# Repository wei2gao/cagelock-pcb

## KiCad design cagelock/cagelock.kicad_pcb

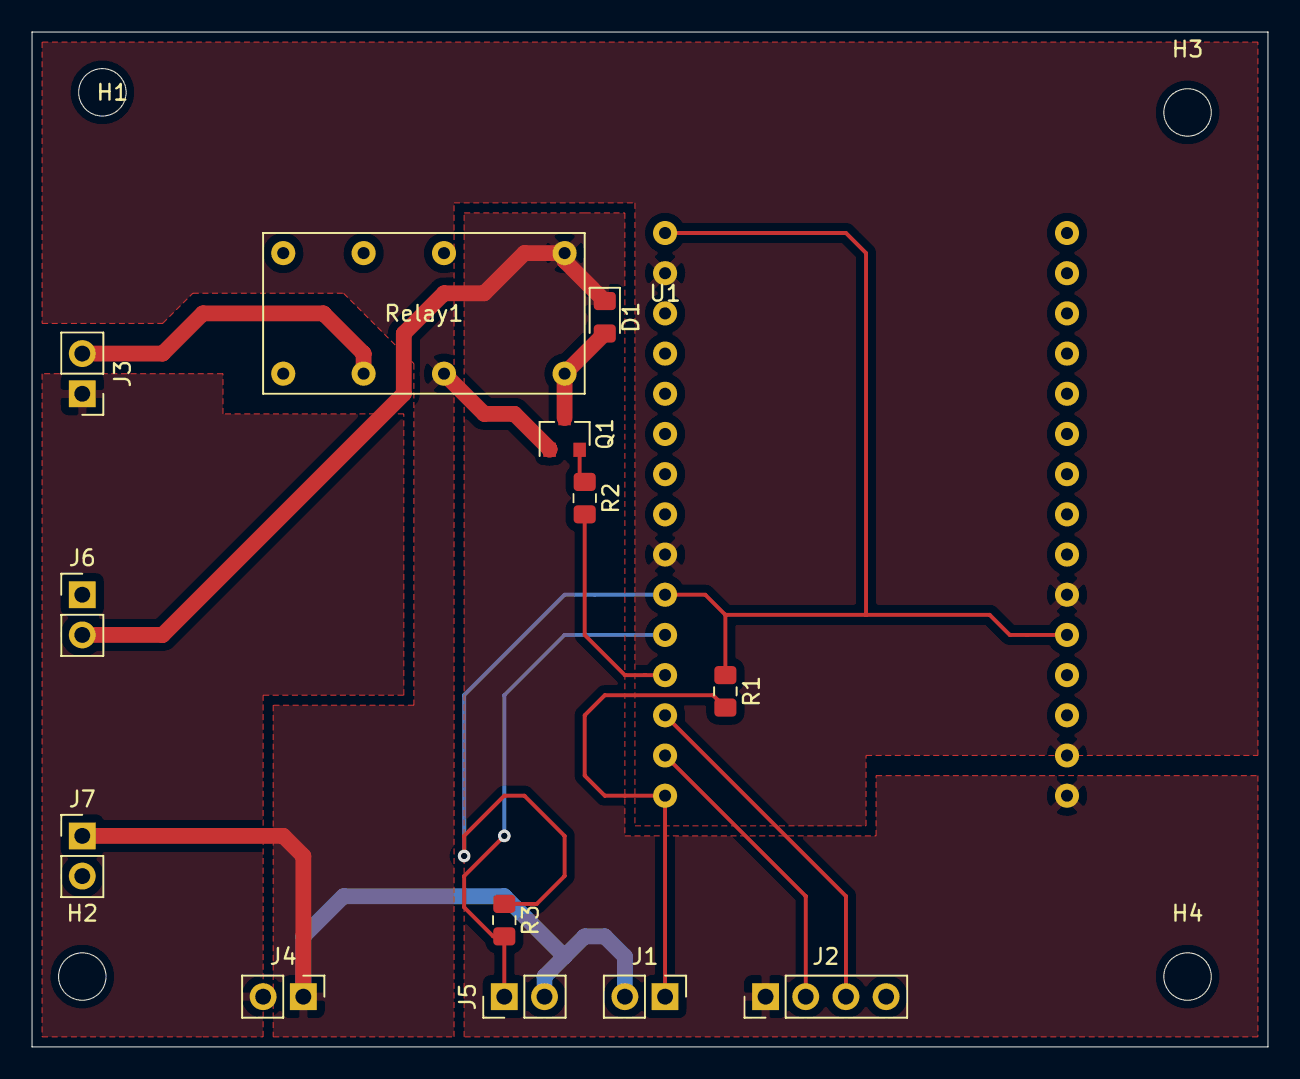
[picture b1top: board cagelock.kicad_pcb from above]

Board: 2 copper layers, 78.1 x 64.1 mm, 18 parts (0 on the bottom side), 12 nets.

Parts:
D1: 1N4148; D_0805_2012Metric_Pad1.15x1.40mm_HandSolder
H1, H2, H3, H4: MountingHole; MountingHole_3mm
J1, J3, J4, J5, J6, J7: Conn_01x02; PinHeader_1x02_P2.54mm_Vertical
J2: Conn_01x04; PinHeader_1x04_P2.54mm_Vertical
Q1: 2N3904; SOT-23
R1, R3: 10k; R_0805_2012Metric_Pad1.15x1.40mm_HandSolder
R2: 1k; R_0805_2012Metric_Pad1.15x1.40mm_HandSolder
Relay1: Relay_SPDT; DS2E-S-DC5V
U1: NodeMCU_v2

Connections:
+3V3: R1.1, R3.1, U1.1, U1.10, U1.26
+12V: D1.1, J2.1, J6.2, Relay1.1, U1.30
+24V: J3.1, J4.2
/BYPASS: J1.1, R1.2, U1.15
/D0: J2.2, U1.14
/D1: J2.3, U1.13
/DOOR_SENSE: J5.1, R3.2, U1.11
/OPEN: R2.2, U1.12
GND: J1.2, J2.4, J4.1, J5.2, J6.1, J7.1, Q1.1, Relay1.5, U1.2, U1.9, U1.25, U1.29
unnamed: D1.2, Q1.3, Relay1.2
unnamed: J3.2, Relay1.3
unnamed: Q1.2, R2.1

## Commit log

2020-03-02 initial commit of files
2020-03-02 Remove unneeded files
2020-03-07 correct pcb
